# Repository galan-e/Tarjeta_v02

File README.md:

# Tarjeta_v02
<pre>Segunda Revision para la tarjeta de desarrollo con FPGA Spartan 6 
Los cambios realizados se centran en:
<ul>
<li> cambio de la IMU
<li> Agrego una tolerancia en borde de la tarjet
<li> Se agrandaron los agujeros de montaje.
<li> Acomodo de capacitores en alimentacion de cada banco del FPGA 
<li> Acomodo de capacitores en la alimentacion de todos los componentes.
</ul>
</pre>
<pre>Se han revisado y corregido los errores en el pcb

<ul>
<li> Trazos pequeños
<li> Trazos cerca de vias
<li> Tolerancia en tre trazos
<li> Nets no conectadas
</ul>
</pre>

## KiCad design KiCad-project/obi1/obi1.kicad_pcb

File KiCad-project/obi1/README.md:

# KiCad Project

The file obi.sch is the main schematic sheet and contains the links to the schematic sheets of all components.

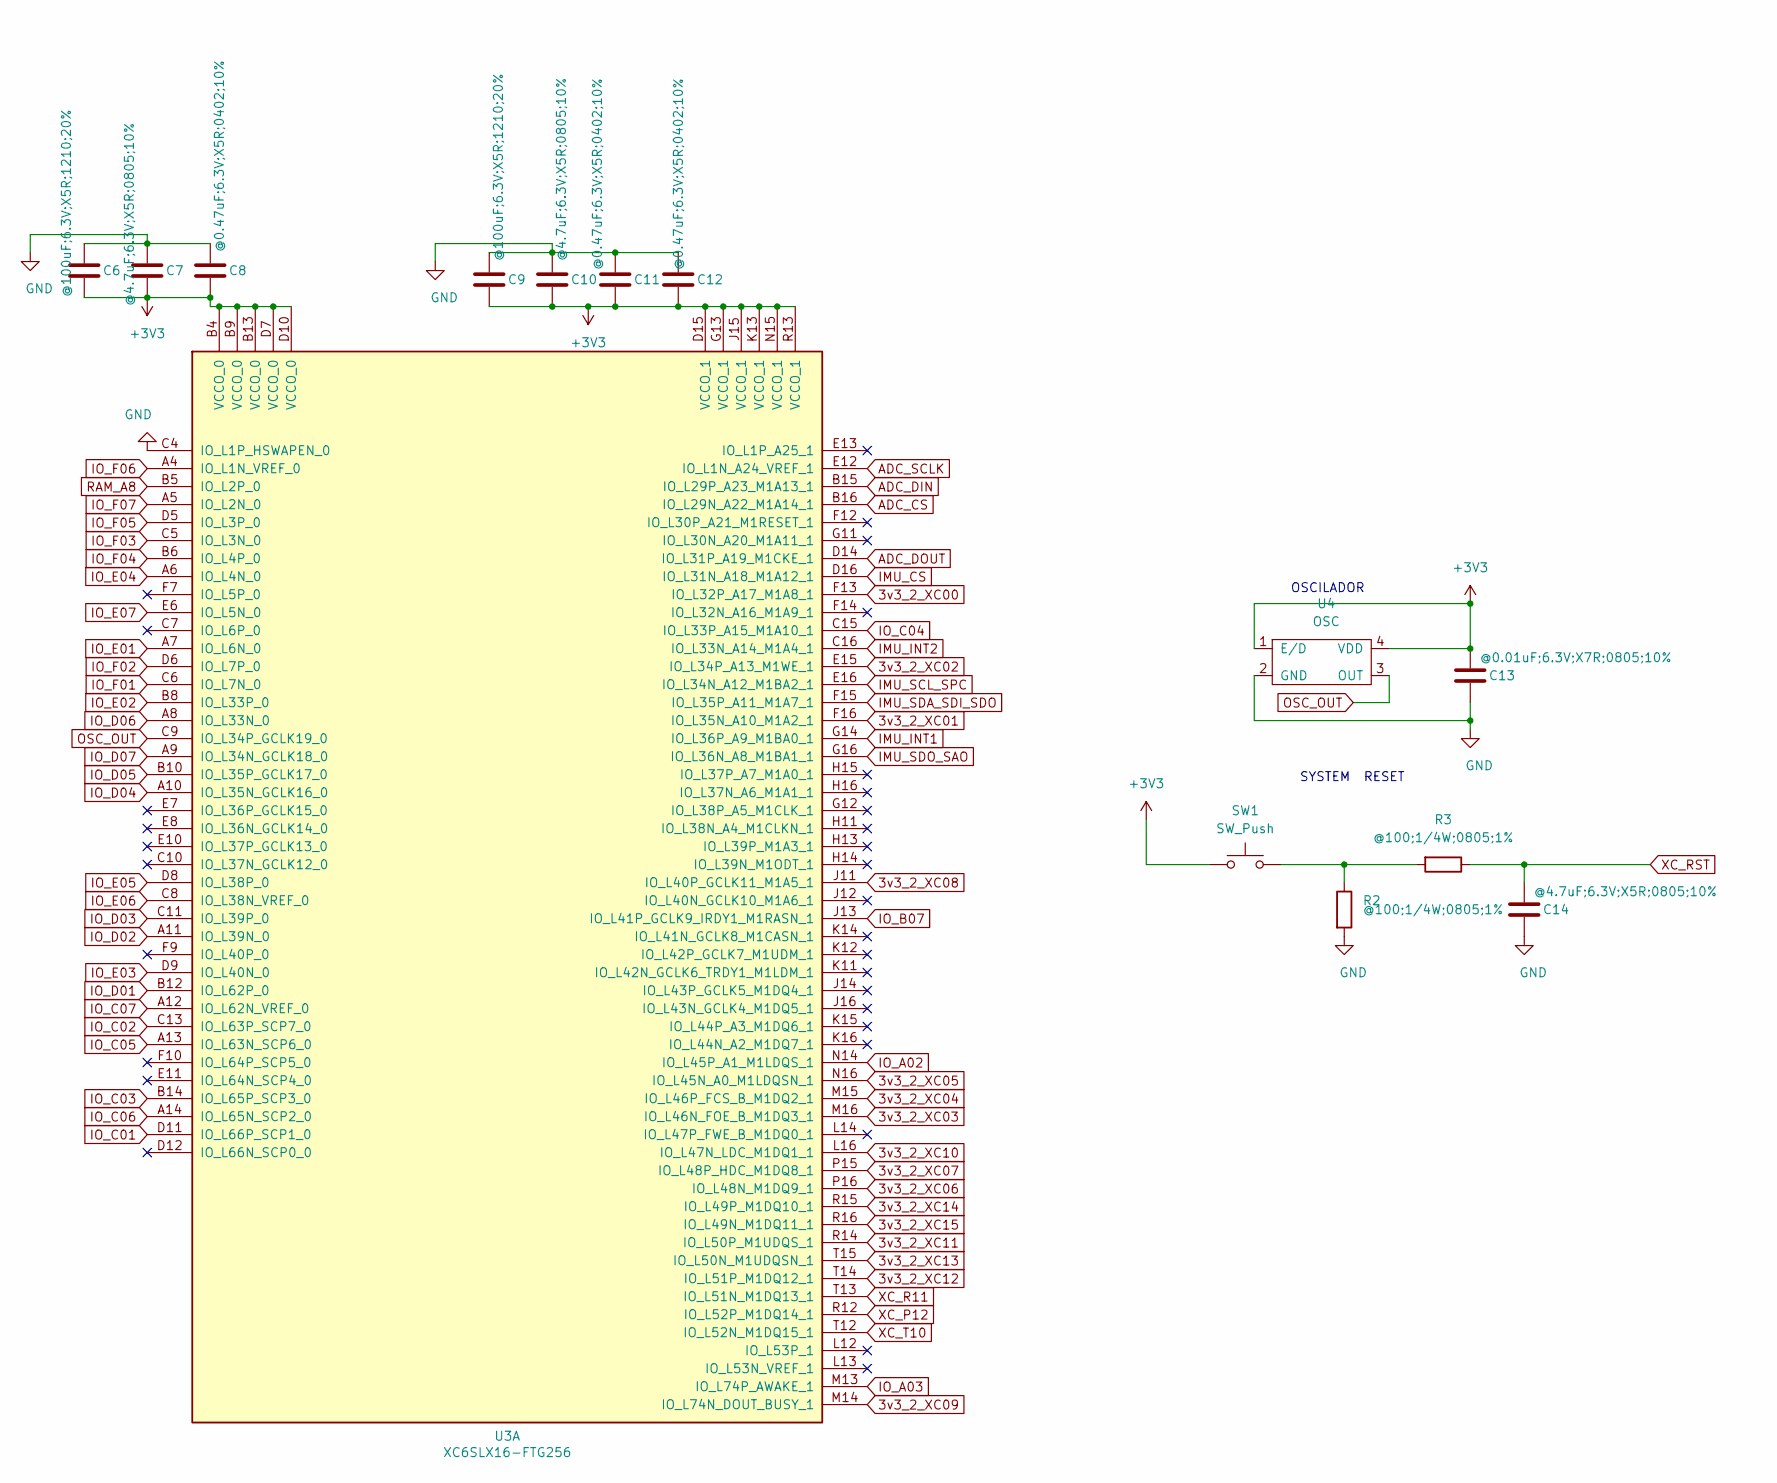
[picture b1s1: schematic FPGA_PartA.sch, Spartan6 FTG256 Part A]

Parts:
C6, C9: @100uF;6.3V;X5R;1210;20%; C_1210_3225Metric_Pad1.33x2.70mm_HandSolder
C7, C10, C14: @4.7uF;6.3V;X5R;0805;10%; C_0805_2012Metric_Pad1.18x1.45mm_HandSolder
C8, C11, C12: @0.47uF;6.3V;X5R;0402;10%; C_0402_1005Metric_Pad0.74x0.62mm_HandSolder
C13: @0.01uF;6.3V;X7R;0805;10%; C_0805_2012Metric_Pad1.18x1.45mm_HandSolder
R2, R3: @100;1/4W;0805;1%; R_0805_2012Metric_Pad1.20x1.40mm_HandSolder
SW1: SW_Push; SW_Push_1P1T_NO_6x6mm_H9.5mm
U3: XC6SLX16-FTG256; BGA-256_17.0x17.0mm_Layout16x16_P1.0mm_Ball0.5mm_Pad0.4mm_N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
U4: OSC; Oscillator_XLH536025.000000I

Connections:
3v3_2_XC00: U3.F13 (IO_L32P_A17_M1A8_1); also elsewhere on the board
3v3_2_XC01: U3.F16 (IO_L35N_A10_M1A2_1); also elsewhere on the board
3v3_2_XC02: U3.E15 (IO_L34P_A13_M1WE_1); also elsewhere on the board
3v3_2_XC03: U3.M16 (IO_L46N_FOE_B_M1DQ3_1); also elsewhere on the board
3v3_2_XC04: U3.M15 (IO_L46P_FCS_B_M1DQ2_1); also elsewhere on the board
3v3_2_XC05: U3.N16 (IO_L45N_A0_M1LDQSN_1); also elsewhere on the board
3v3_2_XC06: U3.P16 (IO_L48N_M1DQ9_1); also elsewhere on the board
3v3_2_XC07: U3.P15 (IO_L48P_HDC_M1DQ8_1); also elsewhere on the board
3v3_2_XC08: U3.J11 (IO_L40P_GCLK11_M1A5_1); also elsewhere on the board
3v3_2_XC09: U3.M14 (IO_L74N_DOUT_BUSY_1); also elsewhere on the board
3v3_2_XC10: U3.L16 (IO_L47N_LDC_M1DQ1_1); also elsewhere on the board
3v3_2_XC11: U3.R14 (IO_L50P_M1UDQS_1); also elsewhere on the board
3v3_2_XC12: U3.T14 (IO_L51P_M1DQ12_1); also elsewhere on the board
3v3_2_XC13: U3.T15 (IO_L50N_M1UDQSN_1); also elsewhere on the board
3v3_2_XC14: U3.R15 (IO_L49P_M1DQ10_1); also elsewhere on the board
3v3_2_XC15: U3.R16 (IO_L49N_M1DQ11_1); also elsewhere on the board
+3V3: C6.2, C7.2, C8.2, C9.2, C10.2, C11.2, C12.2, C13.1, SW1.1, U3.B4 (VCCO_0), U3.B9 (VCCO_0), U3.B13 (VCCO_0), U3.D7 (VCCO_0), U3.D10 (VCCO_0), U3.D15 (VCCO_1), U3.G13 (VCCO_1), U3.J15 (VCCO_1), U3.K13 (VCCO_1), U3.N15 (VCCO_1), U3.R13 (VCCO_1), U4.1 (E/D), U4.4 (VDD); also elsewhere on the board
ADC_CS: U3.B16 (IO_L29N_A22_M1A14_1); also elsewhere on the board
ADC_DIN: U3.B15 (IO_L29P_A23_M1A13_1); also elsewhere on the board
ADC_DOUT: U3.D14 (IO_L31P_A19_M1CKE_1); also elsewhere on the board
ADC_SCLK: U3.E12 (IO_L1N_A24_VREF_1); also elsewhere on the board
GND: C6.1, C7.1, C8.1, C9.1, C10.1, C11.1, C12.1, C13.2, C14.2, R2.2, U3.C4 (IO_L1P_HSWAPEN_0), U4.2 (GND); also elsewhere on the board
IMU_CS: U3.D16 (IO_L31N_A18_M1A12_1); also elsewhere on the board
IMU_INT1: U3.G14 (IO_L36P_A9_M1BA0_1); also elsewhere on the board
IMU_INT2: U3.C16 (IO_L33N_A14_M1A4_1); also elsewhere on the board
IMU_SCL_SPC: U3.E16 (IO_L34N_A12_M1BA2_1); also elsewhere on the board
IMU_SDA_SDI_SDO: U3.F15 (IO_L35P_A11_M1A7_1); also elsewhere on the board
IMU_SDO_SAO: U3.G16 (IO_L36N_A8_M1BA1_1); also elsewhere on the board
IO_A02: U3.N14 (IO_L45P_A1_M1LDQS_1); also elsewhere on the board
IO_A03: U3.M13 (IO_L74P_AWAKE_1); also elsewhere on the board
IO_B07: U3.J13 (IO_L41P_GCLK9_IRDY1_M1RASN_1); also elsewhere on the board
IO_C01: U3.D11 (IO_L66P_SCP1_0); also elsewhere on the board
IO_C02: U3.C13 (IO_L63P_SCP7_0); also elsewhere on the board
IO_C03: U3.B14 (IO_L65P_SCP3_0); also elsewhere on the board
IO_C04: U3.C15 (IO_L33P_A15_M1A10_1); also elsewhere on the board
IO_C05: U3.A13 (IO_L63N_SCP6_0); also elsewhere on the board
IO_C06: U3.A14 (IO_L65N_SCP2_0); also elsewhere on the board
IO_C07: U3.A12 (IO_L62N_VREF_0); also elsewhere on the board
IO_D01: U3.B12 (IO_L62P_0); also elsewhere on the board
IO_D02: U3.A11 (IO_L39N_0); also elsewhere on the board
IO_D03: U3.C11 (IO_L39P_0); also elsewhere on the board
IO_D04: U3.A10 (IO_L35N_GCLK16_0); also elsewhere on the board
IO_D05: U3.B10 (IO_L35P_GCLK17_0); also elsewhere on the board
IO_D06: U3.A8 (IO_L33N_0); also elsewhere on the board
IO_D07: U3.A9 (IO_L34N_GCLK18_0); also elsewhere on the board
IO_E01: U3.A7 (IO_L6N_0); also elsewhere on the board
IO_E02: U3.B8 (IO_L33P_0); also elsewhere on the board
IO_E03: U3.D9 (IO_L40N_0); also elsewhere on the board
IO_E04: U3.A6 (IO_L4N_0); also elsewhere on the board
IO_E05: U3.D8 (IO_L38P_0); also elsewhere on the board
IO_E06: U3.C8 (IO_L38N_VREF_0); also elsewhere on the board
IO_E07: U3.E6 (IO_L5N_0); also elsewhere on the board
IO_F01: U3.C6 (IO_L7N_0); also elsewhere on the board
IO_F02: U3.D6 (IO_L7P_0); also elsewhere on the board
IO_F03: U3.C5 (IO_L3N_0); also elsewhere on the board
IO_F04: U3.B6 (IO_L4P_0); also elsewhere on the board
IO_F05: U3.D5 (IO_L3P_0); also elsewhere on the board
IO_F06: U3.A4 (IO_L1N_VREF_0); also elsewhere on the board
IO_F07: U3.A5 (IO_L2N_0); also elsewhere on the board
unnamed: R2.1, R3.2, SW1.2
OSC_OUT: U3.C9 (IO_L34P_GCLK19_0), U4.3 (OUT)
RAM_A8: U3.B5 (IO_L2P_0); also elsewhere on the board
XC_P12: U3.R12 (IO_L52P_M1DQ14_1); also elsewhere on the board
XC_R11: U3.T13 (IO_L51N_M1DQ13_1); also elsewhere on the board
XC_RST: C14.1, R3.1; also elsewhere on the board
XC_T10: U3.T12 (IO_L52N_M1DQ15_1); also elsewhere on the board

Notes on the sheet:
OSCILADOR
SYSTEM RESET

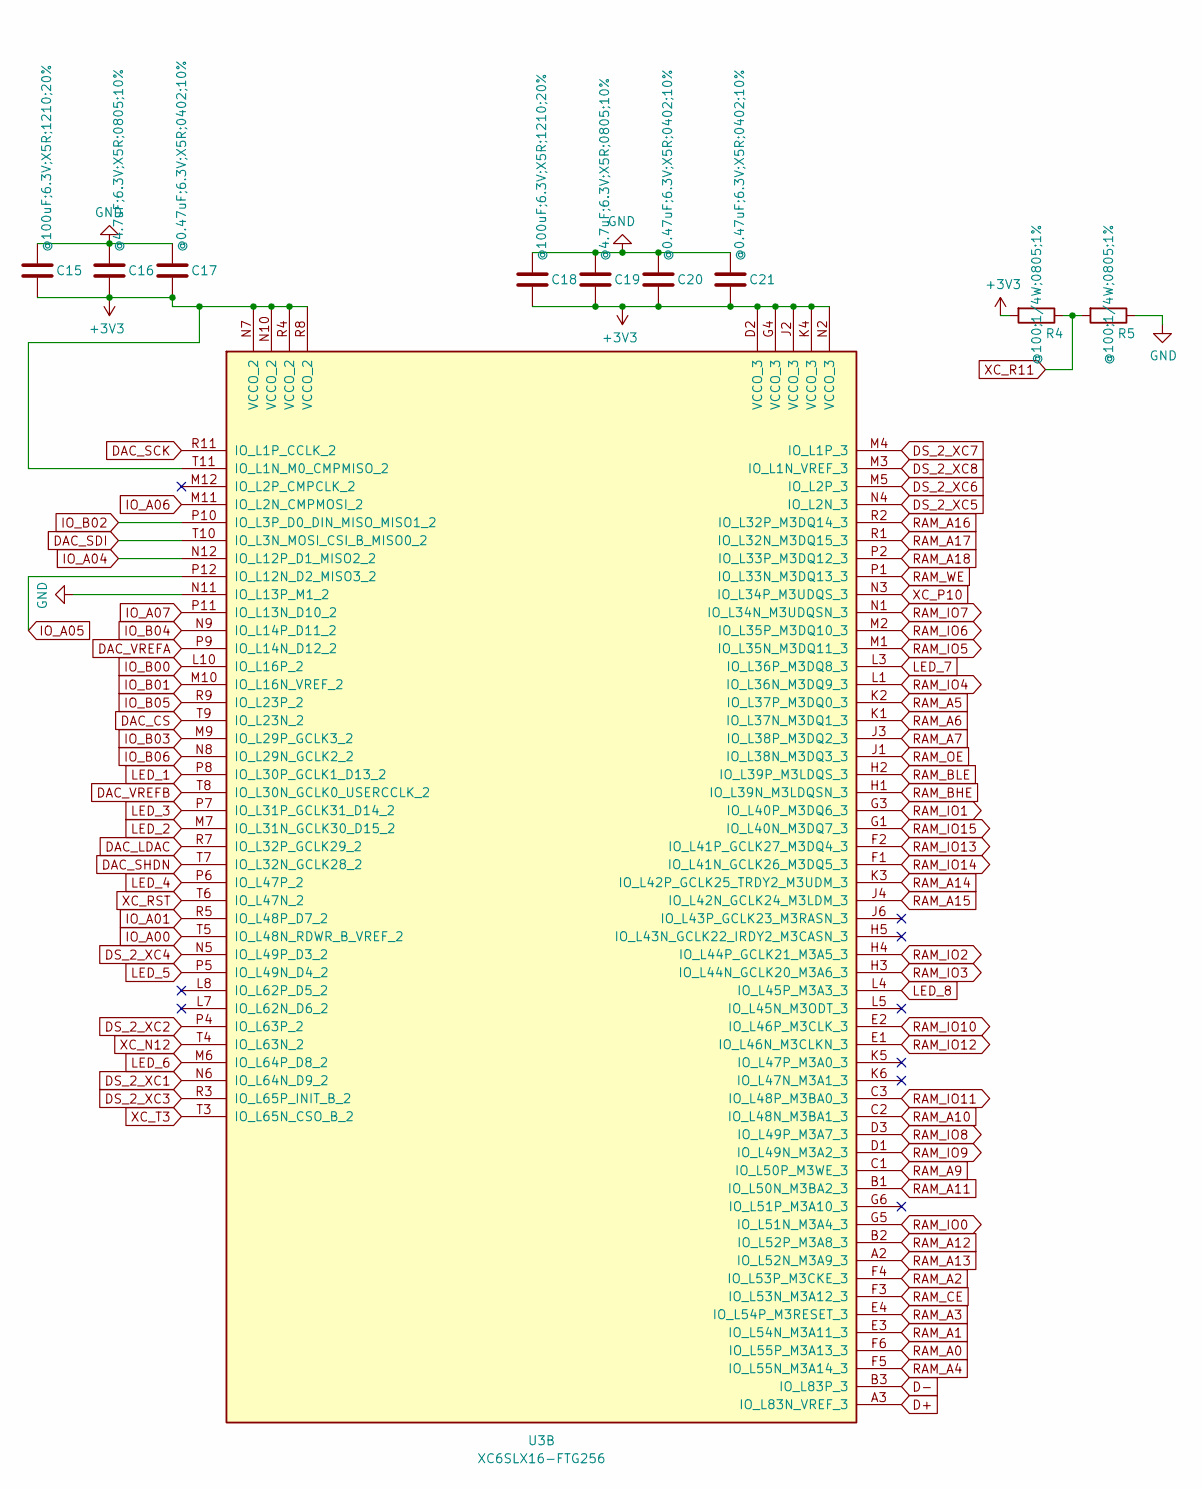
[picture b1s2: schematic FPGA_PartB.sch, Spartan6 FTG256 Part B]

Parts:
C15, C18: @100uF;6.3V;X5R;1210;20%; C_1210_3225Metric_Pad1.33x2.70mm_HandSolder
C16, C19: @4.7uF;6.3V;X5R;0805;10%; C_0805_2012Metric_Pad1.18x1.45mm_HandSolder
C17, C20, C21: @0.47uF;6.3V;X5R;0402;10%; C_0402_1005Metric_Pad0.74x0.62mm_HandSolder
R4, R5: @100;1/4W;0805;1%; R_0805_2012Metric_Pad1.20x1.40mm_HandSolder
U3: XC6SLX16-FTG256; BGA-256_17.0x17.0mm_Layout16x16_P1.0mm_Ball0.5mm_Pad0.4mm_N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

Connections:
+3V3: C15.2, C16.2, C17.2, C18.2, C19.2, C20.2, C21.2, R4.2, U3.D2 (VCCO_3), U3.G4 (VCCO_3), U3.J2 (VCCO_3), U3.K4 (VCCO_3), U3.N2 (VCCO_3), U3.N7 (VCCO_2), U3.N10 (VCCO_2), U3.R4 (VCCO_2), U3.R8 (VCCO_2), U3.T11 (IO_L1N_M0_CMPMISO_2); also elsewhere on the board
D+: U3.A3 (IO_L83N_VREF_3); also elsewhere on the board
D-: U3.B3 (IO_L83P_3); also elsewhere on the board
DAC_CS: U3.T9 (IO_L23N_2); also elsewhere on the board
DAC_LDAC: U3.R7 (IO_L32P_GCLK29_2); also elsewhere on the board
DAC_SCK: U3.R11 (IO_L1P_CCLK_2); also elsewhere on the board
DAC_SDI: U3.T10 (IO_L3N_MOSI_CSI_B_MISO0_2); also elsewhere on the board
DAC_SHDN: U3.T7 (IO_L32N_GCLK28_2); also elsewhere on the board
DAC_VREFA: U3.P9 (IO_L14N_D12_2); also elsewhere on the board
DAC_VREFB: U3.T8 (IO_L30N_GCLK0_USERCCLK_2); also elsewhere on the board
DS_2_XC1: U3.N6 (IO_L64N_D9_2); also elsewhere on the board
DS_2_XC2: U3.P4 (IO_L63P_2); also elsewhere on the board
DS_2_XC3: U3.R3 (IO_L65P_INIT_B_2); also elsewhere on the board
DS_2_XC4: U3.N5 (IO_L49P_D3_2); also elsewhere on the board
DS_2_XC5: U3.N4 (IO_L2N_3); also elsewhere on the board
DS_2_XC6: U3.M5 (IO_L2P_3); also elsewhere on the board
DS_2_XC7: U3.M4 (IO_L1P_3); also elsewhere on the board
DS_2_XC8: U3.M3 (IO_L1N_VREF_3); also elsewhere on the board
GND: C15.1, C16.1, C17.1, C18.1, C19.1, C20.1, C21.1, R5.1, U3.N11 (IO_L13P_M1_2); also elsewhere on the board
IO_A00: U3.T5 (IO_L48N_RDWR_B_VREF_2); also elsewhere on the board
IO_A01: U3.R5 (IO_L48P_D7_2); also elsewhere on the board
IO_A04: U3.N12 (IO_L12P_D1_MISO2_2); also elsewhere on the board
IO_A05: U3.P12 (IO_L12N_D2_MISO3_2); also elsewhere on the board
IO_A06: U3.M11 (IO_L2N_CMPMOSI_2); also elsewhere on the board
IO_A07: U3.P11 (IO_L13N_D10_2); also elsewhere on the board
IO_B00: U3.L10 (IO_L16P_2); also elsewhere on the board
IO_B01: U3.M10 (IO_L16N_VREF_2); also elsewhere on the board
IO_B02: U3.P10 (IO_L3P_D0_DIN_MISO_MISO1_2); also elsewhere on the board
IO_B03: U3.M9 (IO_L29P_GCLK3_2); also elsewhere on the board
IO_B04: U3.N9 (IO_L14P_D11_2); also elsewhere on the board
IO_B05: U3.R9 (IO_L23P_2); also elsewhere on the board
IO_B06: U3.N8 (IO_L29N_GCLK2_2); also elsewhere on the board
LED_1: U3.P8 (IO_L30P_GCLK1_D13_2); also elsewhere on the board
LED_2: U3.M7 (IO_L31N_GCLK30_D15_2); also elsewhere on the board
LED_3: U3.P7 (IO_L31P_GCLK31_D14_2); also elsewhere on the board
LED_4: U3.P6 (IO_L47P_2); also elsewhere on the board
LED_5: U3.P5 (IO_L49N_D4_2); also elsewhere on the board
LED_6: U3.M6 (IO_L64P_D8_2); also elsewhere on the board
LED_7: U3.L3 (IO_L36P_M3DQ8_3); also elsewhere on the board
LED_8: U3.L4 (IO_L45P_M3A3_3); also elsewhere on the board
RAM_A0: U3.F6 (IO_L55P_M3A13_3); also elsewhere on the board
RAM_A1: U3.E3 (IO_L54N_M3A11_3); also elsewhere on the board
RAM_A2: U3.F4 (IO_L53P_M3CKE_3); also elsewhere on the board
RAM_A3: U3.E4 (IO_L54P_M3RESET_3); also elsewhere on the board
RAM_A4: U3.F5 (IO_L55N_M3A14_3); also elsewhere on the board
RAM_A5: U3.K2 (IO_L37P_M3DQ0_3); also elsewhere on the board
RAM_A6: U3.K1 (IO_L37N_M3DQ1_3); also elsewhere on the board
RAM_A7: U3.J3 (IO_L38P_M3DQ2_3); also elsewhere on the board
RAM_A9: U3.C1 (IO_L50P_M3WE_3); also elsewhere on the board
RAM_A10: U3.C2 (IO_L48N_M3BA1_3); also elsewhere on the board
RAM_A11: U3.B1 (IO_L50N_M3BA2_3); also elsewhere on the board
RAM_A12: U3.B2 (IO_L52P_M3A8_3); also elsewhere on the board
RAM_A13: U3.A2 (IO_L52N_M3A9_3); also elsewhere on the board
RAM_A14: U3.K3 (IO_L42P_GCLK25_TRDY2_M3UDM_3); also elsewhere on the board
RAM_A15: U3.J4 (IO_L42N_GCLK24_M3LDM_3); also elsewhere on the board
RAM_A16: U3.R2 (IO_L32P_M3DQ14_3); also elsewhere on the board
RAM_A17: U3.R1 (IO_L32N_M3DQ15_3); also elsewhere on the board
RAM_A18: U3.P2 (IO_L33P_M3DQ12_3); also elsewhere on the board
RAM_BHE: U3.H1 (IO_L39N_M3LDQSN_3); also elsewhere on the board
RAM_BLE: U3.H2 (IO_L39P_M3LDQS_3); also elsewhere on the board
RAM_CE: U3.F3 (IO_L53N_M3A12_3); also elsewhere on the board
RAM_IO0: U3.G5 (IO_L51N_M3A4_3); also elsewhere on the board
RAM_IO1: U3.G3 (IO_L40P_M3DQ6_3); also elsewhere on the board
RAM_IO2: U3.H4 (IO_L44P_GCLK21_M3A5_3); also elsewhere on the board
RAM_IO3: U3.H3 (IO_L44N_GCLK20_M3A6_3); also elsewhere on the board
RAM_IO4: U3.L1 (IO_L36N_M3DQ9_3); also elsewhere on the board
RAM_IO5: U3.M1 (IO_L35N_M3DQ11_3); also elsewhere on the board
RAM_IO6: U3.M2 (IO_L35P_M3DQ10_3); also elsewhere on the board
RAM_IO7: U3.N1 (IO_L34N_M3UDQSN_3); also elsewhere on the board
RAM_IO8: U3.D3 (IO_L49P_M3A7_3); also elsewhere on the board
RAM_IO9: U3.D1 (IO_L49N_M3A2_3); also elsewhere on the board
RAM_IO10: U3.E2 (IO_L46P_M3CLK_3); also elsewhere on the board
RAM_IO11: U3.C3 (IO_L48P_M3BA0_3); also elsewhere on the board
RAM_IO12: U3.E1 (IO_L46N_M3CLKN_3); also elsewhere on the board
RAM_IO13: U3.F2 (IO_L41P_GCLK27_M3DQ4_3); also elsewhere on the board
RAM_IO14: U3.F1 (IO_L41N_GCLK26_M3DQ5_3); also elsewhere on the board
RAM_IO15: U3.G1 (IO_L40N_M3DQ7_3); also elsewhere on the board
RAM_OE: U3.J1 (IO_L38N_M3DQ3_3); also elsewhere on the board
RAM_WE: U3.P1 (IO_L33N_M3DQ13_3); also elsewhere on the board
XC_N12: U3.T4 (IO_L63N_2); also elsewhere on the board
XC_P10: U3.N3 (IO_L34P_M3UDQS_3); also elsewhere on the board
XC_R11: R4.1, R5.2; also elsewhere on the board
XC_RST: U3.T6 (IO_L47N_2); also elsewhere on the board
XC_T3: U3.T3 (IO_L65N_CSO_B_2); also elsewhere on the board

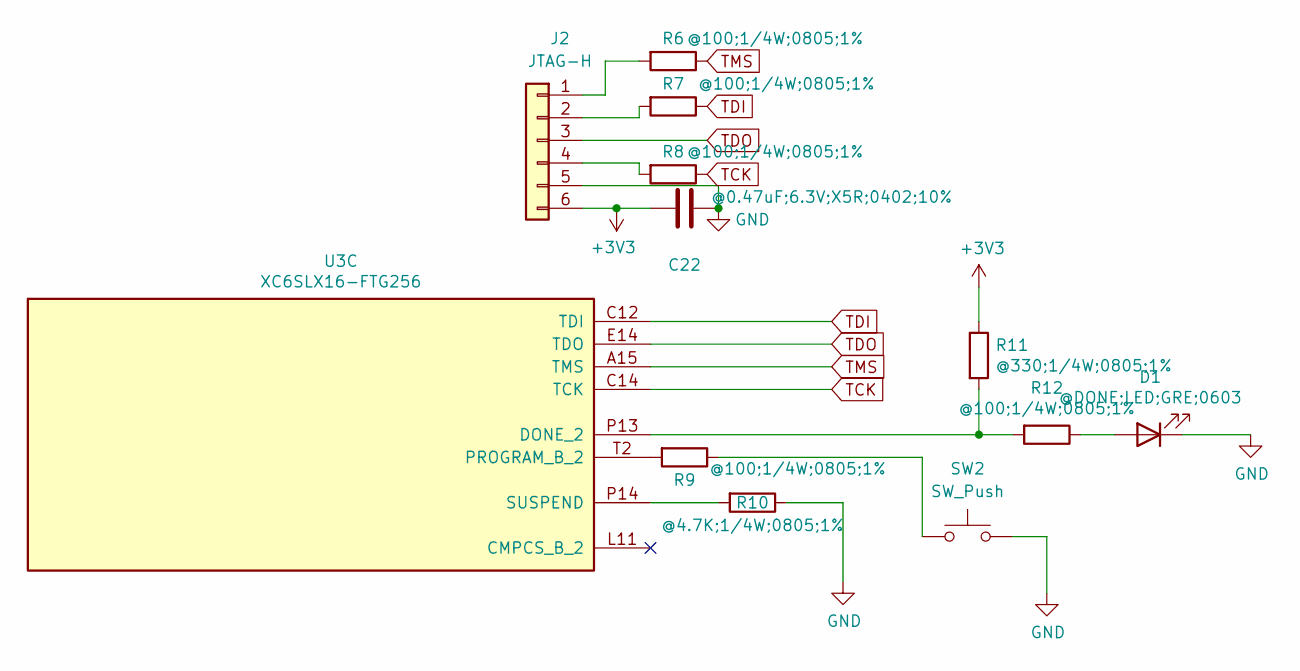
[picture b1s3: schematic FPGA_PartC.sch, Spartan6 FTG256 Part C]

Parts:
C22: @0.47uF;6.3V;X5R;0402;10%; C_0402_1005Metric_Pad0.74x0.62mm_HandSolder
D1: @DONE;LED;GRE;0603; LED_0603_1608Metric_Pad1.05x0.95mm_HandSolder
J2: JTAG-H; PinSocket_1x06_P2.54mm_Vertical
R6, R7, R8, R9, R12: @100;1/4W;0805;1%; R_0805_2012Metric_Pad1.20x1.40mm_HandSolder
R10: @4.7K;1/4W;0805;1%; R_0805_2012Metric_Pad1.20x1.40mm_HandSolder
R11: @330;1/4W;0805;1%; R_0805_2012Metric_Pad1.20x1.40mm_HandSolder
SW2: SW_Push; SW_Push_1P1T_NO_6x6mm_H9.5mm
U3: XC6SLX16-FTG256; BGA-256_17.0x17.0mm_Layout16x16_P1.0mm_Ball0.5mm_Pad0.4mm_N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

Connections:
+3V3: C22.2, J2.6, R11.1; also elsewhere on the board
GND: C22.1, D1.1 (K), J2.5, R10.1, SW2.2; also elsewhere on the board
unnamed: D1.2 (A), R12.1
unnamed: J2.1, R6.2
unnamed: J2.2, R7.2
unnamed: J2.4, R8.2
unnamed: R9.1, SW2.1
unnamed: R9.2, U3.T2 (PROGRAM_B_2)
unnamed: R10.2, U3.P14 (SUSPEND)
unnamed: R11.2, R12.2, U3.P13 (DONE_2)
TCK: R8.1, U3.C14 (TCK)
TDI: R7.1, U3.C12 (TDI)
TDO: J2.3, U3.E14 (TDO)
TMS: R6.1, U3.A15 (TMS)

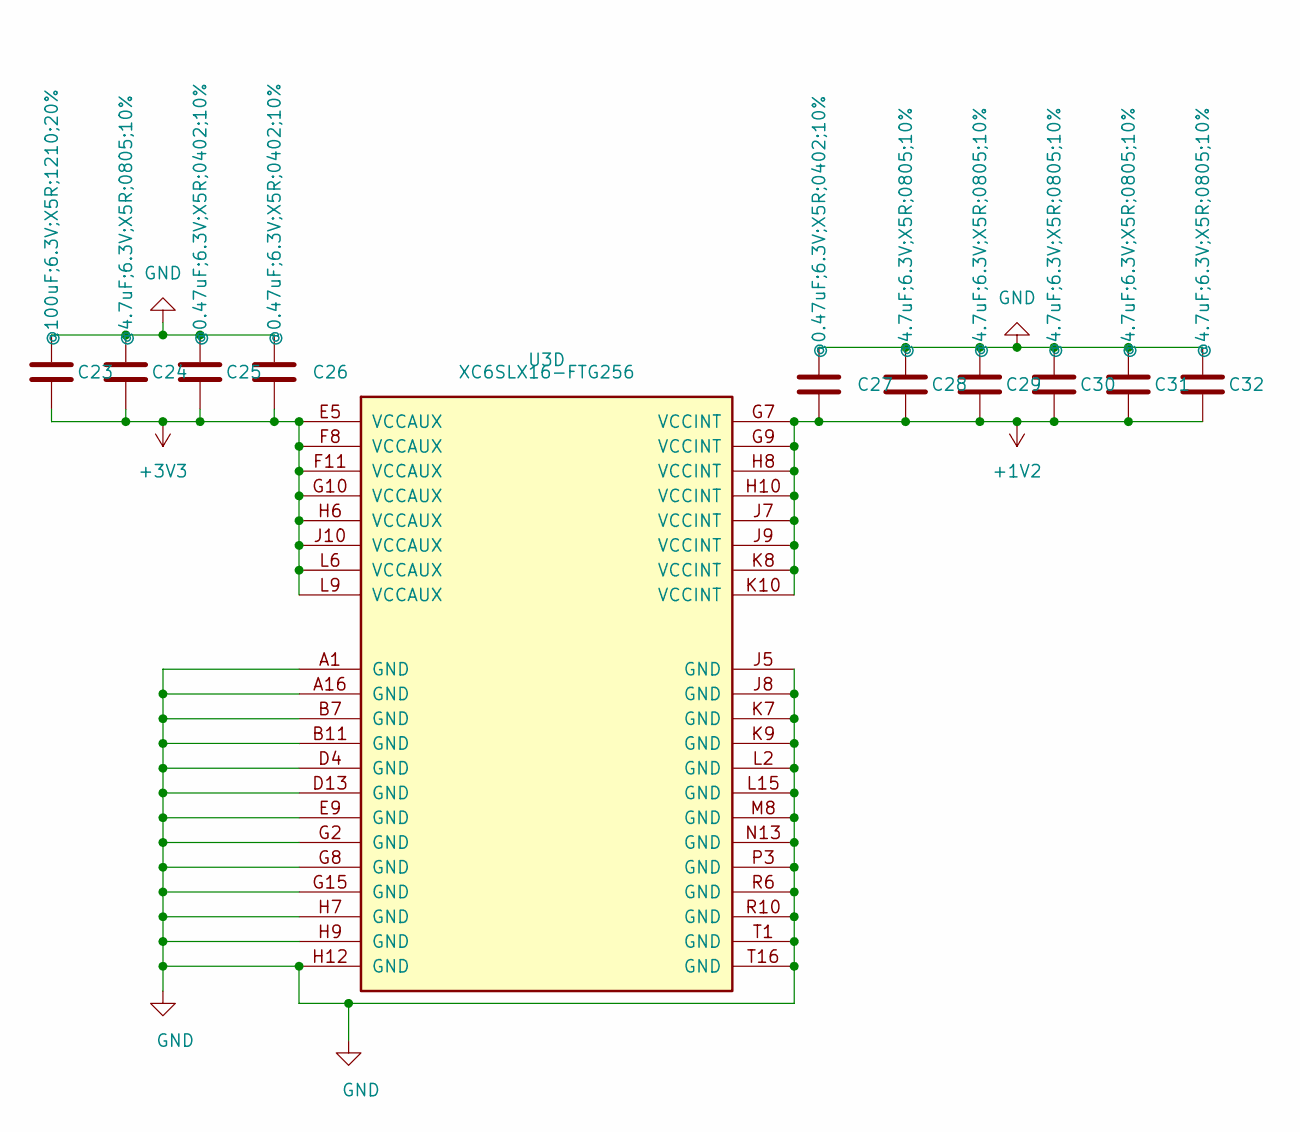
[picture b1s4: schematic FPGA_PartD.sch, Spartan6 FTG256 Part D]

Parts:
C23: @100uF;6.3V;X5R;1210;20%; C_1210_3225Metric_Pad1.33x2.70mm_HandSolder
C24, C28, C29, C30, C31, C32: @4.7uF;6.3V;X5R;0805;10%; C_0805_2012Metric_Pad1.18x1.45mm_HandSolder
C25, C26, C27: @0.47uF;6.3V;X5R;0402;10%; C_0402_1005Metric_Pad0.74x0.62mm_HandSolder
U3: XC6SLX16-FTG256; BGA-256_17.0x17.0mm_Layout16x16_P1.0mm_Ball0.5mm_Pad0.4mm_N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

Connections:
+1V2: C27.2, C28.2, C29.2, C30.2, C31.2, C32.2, U3.G7 (VCCINT), U3.G9 (VCCINT), U3.H8 (VCCINT), U3.H10 (VCCINT), U3.J7 (VCCINT), U3.J9 (VCCINT), U3.K8 (VCCINT), U3.K10 (VCCINT); also elsewhere on the board
+3V3: C23.2, C24.2, C25.2, C26.2, U3.E5 (VCCAUX), U3.F8 (VCCAUX), U3.F11 (VCCAUX), U3.G10 (VCCAUX), U3.H6 (VCCAUX), U3.J10 (VCCAUX), U3.L6 (VCCAUX), U3.L9 (VCCAUX); also elsewhere on the board
GND: C23.1, C24.1, C25.1, C26.1, C27.1, C28.1, C29.1, C30.1, C31.1, C32.1, U3.A1 (GND), U3.A16 (GND), U3.B7 (GND), U3.B11 (GND), U3.D4 (GND), U3.D13 (GND), U3.E9 (GND), U3.G2 (GND), U3.G8 (GND), U3.G15 (GND), U3.H7 (GND), U3.H9 (GND), U3.H12 (GND), U3.J5 (GND), U3.J8 (GND), U3.K7 (GND), U3.K9 (GND), U3.L2 (GND), U3.L15 (GND), U3.M8 (GND), U3.N13 (GND), U3.P3 (GND), U3.R6 (GND), U3.R10 (GND), U3.T1 (GND), U3.T16 (GND); also elsewhere on the board

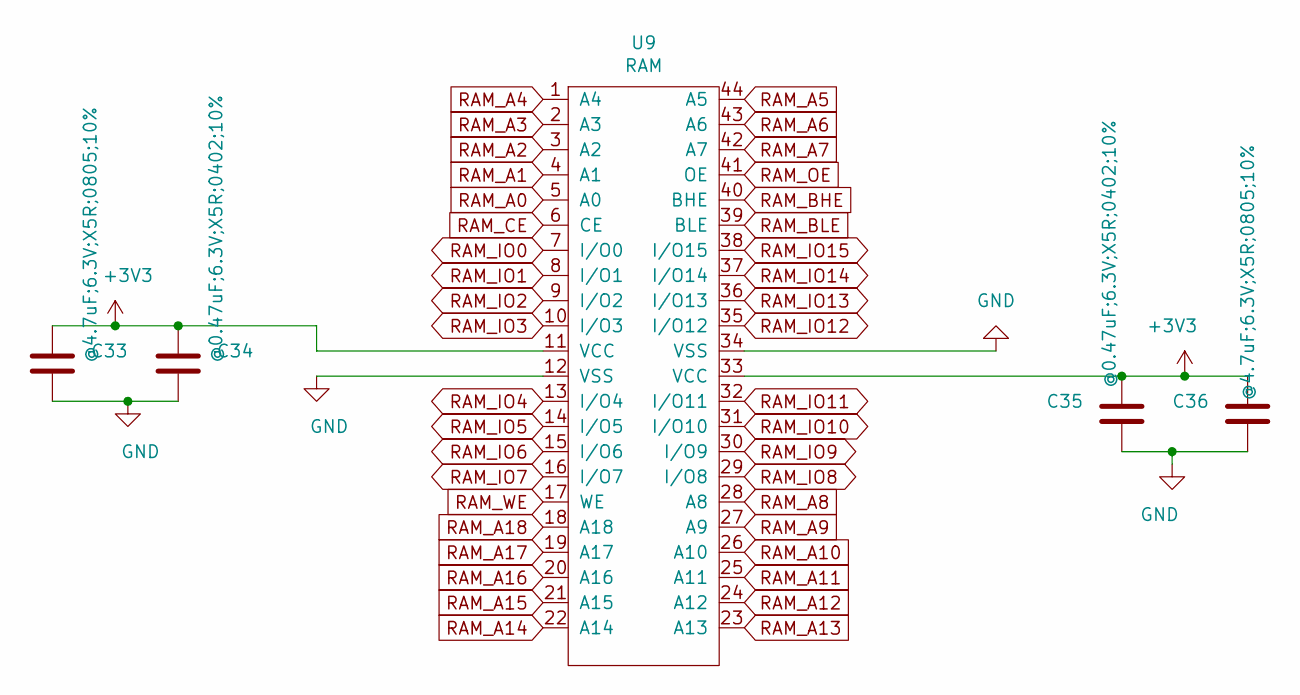
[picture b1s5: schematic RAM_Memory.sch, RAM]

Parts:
C33, C36: @4.7uF;6.3V;X5R;0805;10%; C_0805_2012Metric_Pad1.18x1.45mm_HandSolder
C34, C35: @0.47uF;6.3V;X5R;0402;10%; C_0402_1005Metric_Pad0.74x0.62mm_HandSolder
U9: RAM; SOP80P1176X120-44N

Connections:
+3V3: C33.1, C34.1, C35.1, C36.1, U9.11 (VCC), U9.33 (VCC); also elsewhere on the board
GND: C33.2, C34.2, C35.2, C36.2, U9.12 (VSS), U9.34 (VSS); also elsewhere on the board
RAM_A0: U9.5 (A0); also elsewhere on the board
RAM_A1: U9.4 (A1); also elsewhere on the board
RAM_A2: U9.3 (A2); also elsewhere on the board
RAM_A3: U9.2 (A3); also elsewhere on the board
RAM_A4: U9.1 (A4); also elsewhere on the board
RAM_A5: U9.44 (A5); also elsewhere on the board
RAM_A6: U9.43 (A6); also elsewhere on the board
RAM_A7: U9.42 (A7); also elsewhere on the board
RAM_A8: U9.28 (A8); also elsewhere on the board
RAM_A9: U9.27 (A9); also elsewhere on the board
RAM_A10: U9.26 (A10); also elsewhere on the board
RAM_A11: U9.25 (A11); also elsewhere on the board
RAM_A12: U9.24 (A12); also elsewhere on the board
RAM_A13: U9.23 (A13); also elsewhere on the board
RAM_A14: U9.22 (A14); also elsewhere on the board
RAM_A15: U9.21 (A15); also elsewhere on the board
RAM_A16: U9.20 (A16); also elsewhere on the board
RAM_A17: U9.19 (A17); also elsewhere on the board
RAM_A18: U9.18 (A18); also elsewhere on the board
RAM_BHE: U9.40 (BHE); also elsewhere on the board
RAM_BLE: U9.39 (BLE); also elsewhere on the board
RAM_CE: U9.6 (CE); also elsewhere on the board
RAM_IO0: U9.7 (I/O0); also elsewhere on the board
RAM_IO1: U9.8 (I/O1); also elsewhere on the board
RAM_IO2: U9.9 (I/O2); also elsewhere on the board
RAM_IO3: U9.10 (I/O3); also elsewhere on the board
RAM_IO4: U9.13 (I/O4); also elsewhere on the board
RAM_IO5: U9.14 (I/O5); also elsewhere on the board
RAM_IO6: U9.15 (I/O6); also elsewhere on the board
RAM_IO7: U9.16 (I/O7); also elsewhere on the board
RAM_IO8: U9.29 (I/O8); also elsewhere on the board
RAM_IO9: U9.30 (I/O9); also elsewhere on the board
RAM_IO10: U9.31 (I/O10); also elsewhere on the board
RAM_IO11: U9.32 (I/O11); also elsewhere on the board
RAM_IO12: U9.35 (I/O12); also elsewhere on the board
RAM_IO13: U9.36 (I/O13); also elsewhere on the board
RAM_IO14: U9.37 (I/O14); also elsewhere on the board
RAM_IO15: U9.38 (I/O15); also elsewhere on the board
RAM_OE: U9.41 (OE); also elsewhere on the board
RAM_WE: U9.17 (WE); also elsewhere on the board

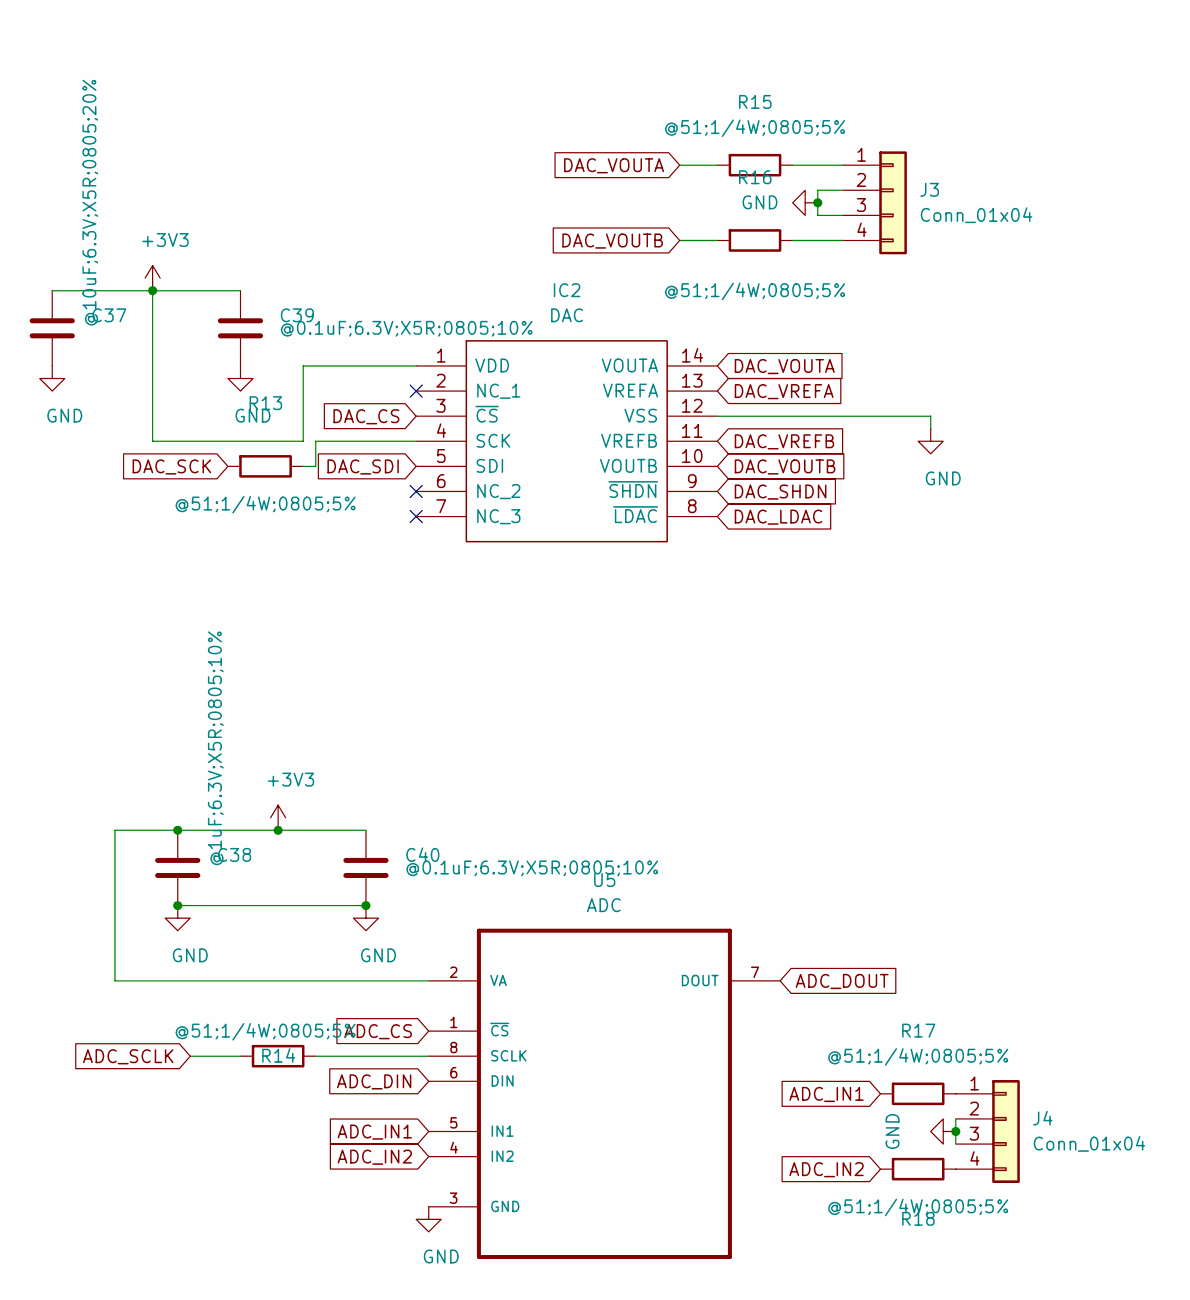
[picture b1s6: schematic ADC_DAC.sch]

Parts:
C37: @10uF;6.3V;X5R;0805;20%; C_0805_2012Metric_Pad1.18x1.45mm_HandSolder
C38: @1uF;6.3V;X5R;0805;10%; C_0805_2012Metric_Pad1.18x1.45mm_HandSolder
C39, C40: @0.1uF;6.3V;X5R;0805;10%; C_0805_2012Metric_Pad1.18x1.45mm_HandSolder
IC2: DAC; SOP65P640X120-14N; Manufacturer_Part_Number MCP4922T-E/ST; Mouser Part Number 579-MCP4922T-E/ST
J3, J4: Conn_01x04; PinSocket_1x04_P2.54mm_Vertical
R13, R14, R15, R16, R17, R18: @51;1/4W;0805;5%; R_0805_2012Metric_Pad1.20x1.40mm_HandSolder
U5: ADC; SOP65P490X109-8N

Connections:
+3V3: C37.1, C38.1, C39.1, C40.1, IC2.1 (VDD), U5.2 (VA); also elsewhere on the board
ADC_CS: U5.1 (~CS); also elsewhere on the board
ADC_DIN: U5.6 (DIN); also elsewhere on the board
ADC_DOUT: U5.7 (DOUT); also elsewhere on the board
ADC_IN1: R17.2, U5.5 (IN1)
ADC_IN2: R18.2, U5.4 (IN2)
ADC_SCLK: R14.2; also elsewhere on the board
DAC_CS: IC2.3 (~CS); also elsewhere on the board
DAC_LDAC: IC2.8 (~LDAC); also elsewhere on the board
DAC_SCK: R13.2; also elsewhere on the board
DAC_SDI: IC2.5 (SDI); also elsewhere on the board
DAC_SHDN: IC2.9 (~SHDN); also elsewhere on the board
DAC_VOUTA: IC2.14 (VOUTA), R15.2
DAC_VOUTB: IC2.10 (VOUTB), R16.2
DAC_VREFA: IC2.13 (VREFA); also elsewhere on the board
DAC_VREFB: IC2.11 (VREFB); also elsewhere on the board
GND: C37.2, C38.2, C39.2, C40.2, IC2.12 (VSS), J3.2, J3.3, J4.2, J4.3, U5.3 (GND); also elsewhere on the board
unnamed: IC2.4 (SCK), R13.1
unnamed: J3.1, R15.1
unnamed: J3.4, R16.1
unnamed: J4.1, R17.1
unnamed: J4.4, R18.1
unnamed: R14.1, U5.8 (SCLK)

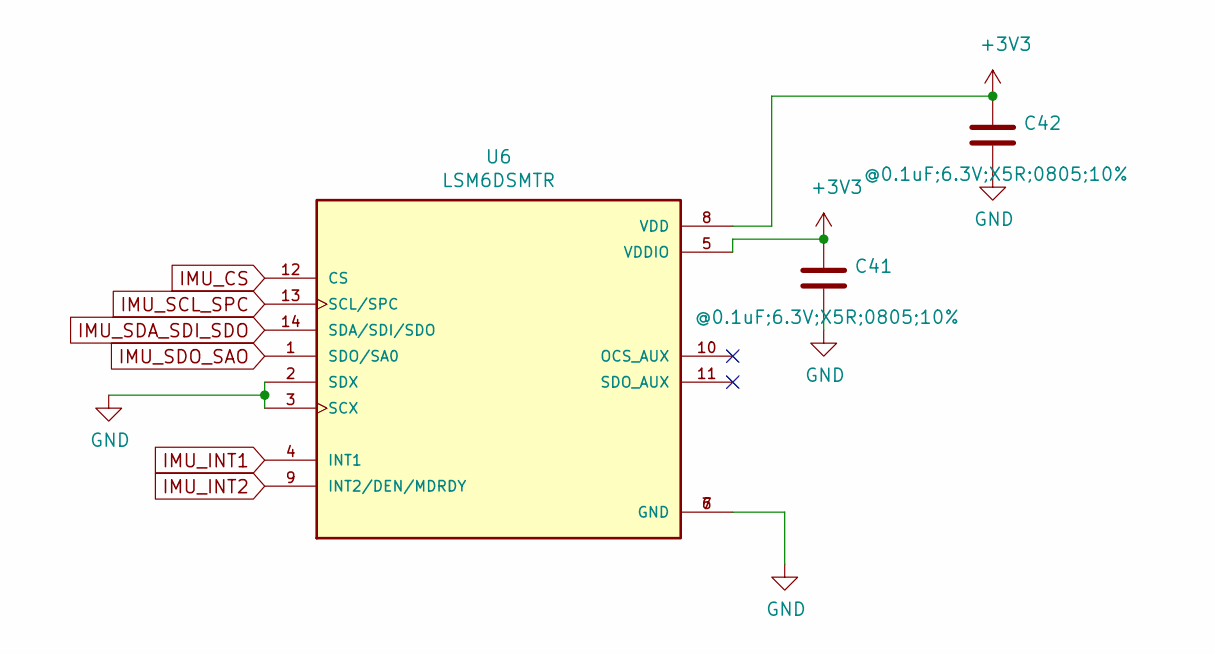
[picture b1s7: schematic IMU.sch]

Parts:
C41, C42: @0.1uF;6.3V;X5R;0805;10%; C_0805_2012Metric_Pad1.18x1.45mm_HandSolder
U6: LSM6DSMTR; PQFN50P300X250X86-14N; PARTREV Rev 7

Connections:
+3V3: C41.1, C42.1, U6.5 (VDDIO), U6.8 (VDD); also elsewhere on the board
GND: C41.2, C42.2, U6.2 (SDX), U6.3 (SCX), U6.6 (GND), U6.7 (GND); also elsewhere on the board
IMU_CS: U6.12 (CS); also elsewhere on the board
IMU_INT1: U6.4 (INT1); also elsewhere on the board
IMU_INT2: U6.9 (INT2/DEN/MDRDY); also elsewhere on the board
IMU_SCL_SPC: U6.13 (SCL/SPC); also elsewhere on the board
IMU_SDA_SDI_SDO: U6.14 (SDA/SDI/SDO); also elsewhere on the board
IMU_SDO_SAO: U6.1 (SDO/SA0); also elsewhere on the board
